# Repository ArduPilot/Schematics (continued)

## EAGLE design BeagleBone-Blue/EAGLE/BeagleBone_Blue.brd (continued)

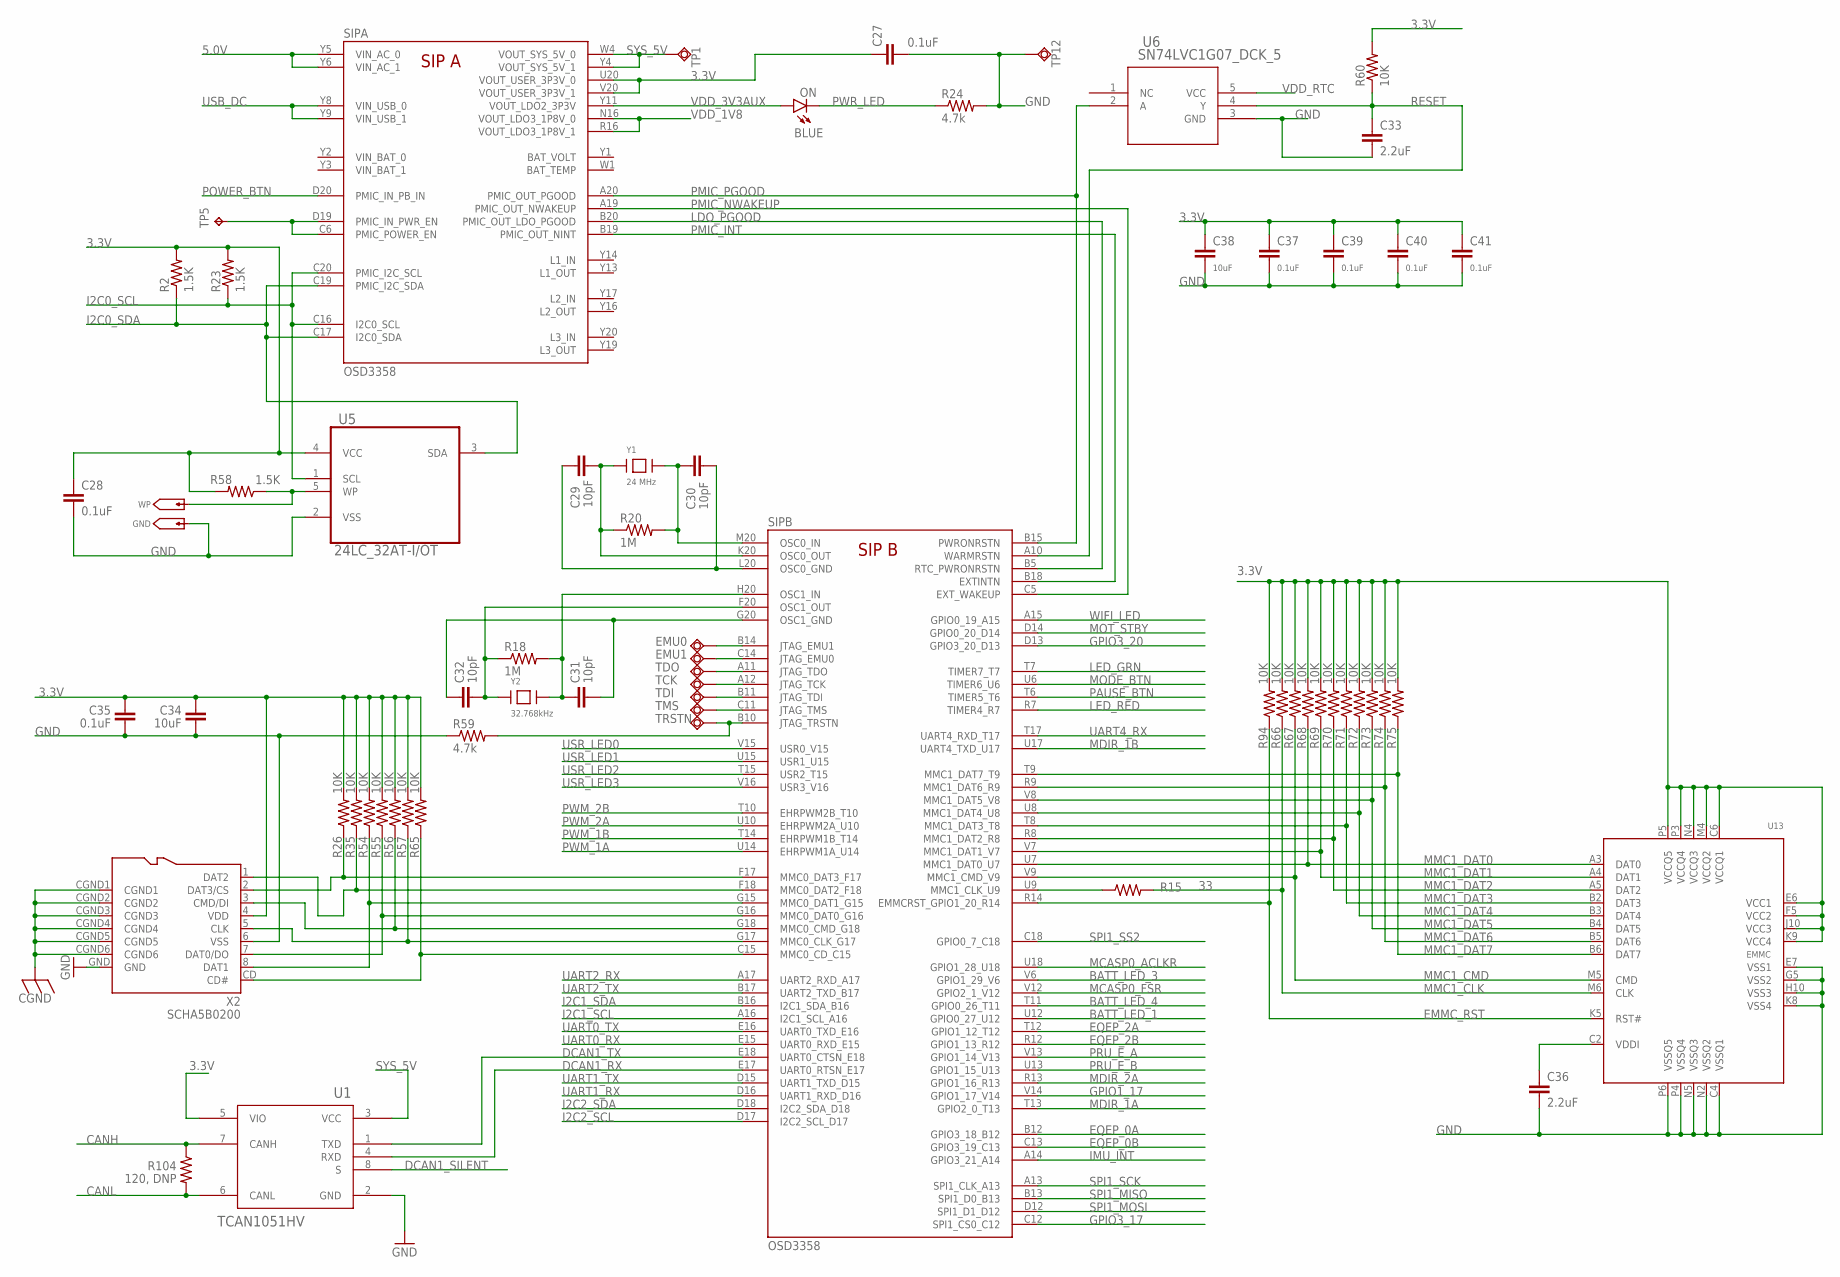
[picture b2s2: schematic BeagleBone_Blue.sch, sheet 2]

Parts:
C27, C28, C35, C37, C39, C40, C41: 0.1uF; 0402-CAP
C29, C30, C31, C32: 10pF; 0402-CAP
C33, C36: 2.2uF; 0402-CAP
C34, C38: 10uF; 0805
EMU0, EMU1: TPSQB1,27; B1,27
GND: GHI2_TESTPAD/W_HOLE_1X1
ON: BLUE; BEAGLEBONE_BLUE_LED-0603
R2, R23, R58: 1.5K; 0402-RES
R15: 33; 0402-RES
R18, R20: 1M; 0402-RES
R24, R59: 4.7k; 0402-RES
R26, R35, R54, R55, R56, R57, R60, R65, R66, R67, R68, R69, R70, R71, R72, R73, R74, R75, R94: 10K; 0402-RES
R104: 120, DNP; 0603-RES
SIP: OSD3358; BEAGLEBONE_BLUE_OSD3358
TCK: TPSQB1,27; B1,27
TDI: TPSQB1,27; B1,27
TDO: TPSQB1,27; B1,27
TMS: TPSQB1,27; B1,27
TP1, TP12: TPSQB1,27; B1,27
TP5: TPB0,65; BEAGLEBONE_BLUE_B0,65
TRSTN: TPSQB1,27; B1,27
U1: TCAN1051HV; BEAGLEBONE_BLUE_D8
U5: 24LC_32AT-I/OT; SOT95P290X145-5N
U6: SN74LVC1G07_DCK_5; BEAGLEBONE_BLUE_DCK5
U13: EMMC; MICRON_EMMC_153
WP: GHI2_TESTPAD/W_HOLE_1X1
X2: SCHA5B0200
Y1: 24 MHz; CRYSTAL_5X3.2MM
Y2: 32.768kHz; CRYSTAL_3.2X1.5

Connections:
3.3V: C27.1, C28.1, C34.2, C35.2, C37.1, C38.1, C39.1, C40.1, C41.1, R2.2, R23.2, R26.2, R35.2, R54.2, R55.2, R56.2, R57.2, R58.2, R60.2, R65.2, R66.2, R67.2, R68.2, R69.2, R70.2, R71.2, R72.2, R73.2, R74.2, R75.2, R94.2, SIP.U20 (VOUT_USER_3P3V_0), SIP.V20 (VOUT_USER_3P3V_1), U1.5 (VIO), U5.4 (VCC), U13.C6 (VCCQ1), U13.E6 (VCC1), U13.F5 (VCC2), U13.J10 (VCC3), U13.K9 (VCC4), U13.M4 (VCCQ2), U13.N4 (VCCQ3), U13.P3 (VCCQ4), U13.P5 (VCCQ5), X2.4 (VDD); also elsewhere on the board
5.0V: SIP.Y5 (VIN_AC_0), SIP.Y6 (VIN_AC_1); also elsewhere on the board
BATT_LED_1: SIP.U12 (GPIO0_27_U12); also elsewhere on the board
BATT_LED_3: SIP.V6 (GPIO1_29_V6); also elsewhere on the board
BATT_LED_4: SIP.T11 (GPIO0_26_T11); also elsewhere on the board
CANH: R104.1, U1.7 (CANH); also elsewhere on the board
CANL: R104.2, U1.6 (CANL); also elsewhere on the board
CGND: X2.CGND1, X2.CGND2, X2.CGND3, X2.CGND4, X2.CGND5, X2.CGND6; also elsewhere on the board
DCAN1_RX: SIP.E17 (UART0_RTSN_E17), U1.4 (RXD)
DCAN1_SILENT: U1.8 (S); also elsewhere on the board
DCAN1_TX: SIP.E18 (UART0_CTSN_E18), U1.1 (TXD)
EMMC_RST: R94.1, SIP.R14 (EMMCRST_GPIO1_20_R14), U13.K5 (RST#)
EQEP_0A: SIP.B12 (GPIO3_18_B12); also elsewhere on the board
EQEP_0B: SIP.C13 (GPIO3_19_C13); also elsewhere on the board
EQEP_2A: SIP.T12 (GPIO1_12_T12); also elsewhere on the board
EQEP_2B: SIP.R12 (GPIO1_13_R12); also elsewhere on the board
GND: C27.2, C28.2, C33.2, C34.1, C35.1, C36.2, C37.2, C38.2, C39.2, C40.2, C41.2, GND.P$1, R24.2, R59.1, TP12.TP, U1.2 (GND), U5.2 (VSS), U6.3 (GND), U13.C4 (VSSQ1), U13.E7 (VSS1), U13.G5 (VSS2), U13.H10 (VSS3), U13.K8 (VSS4), U13.N2 (VSSQ2), U13.N5 (VSSQ3), U13.P4 (VSSQ4), U13.P6 (VSSQ5), X2.6 (VSS), X2.GND; also elsewhere on the board
GPIO1_17: SIP.V14 (GPIO1_17_V14); also elsewhere on the board
GPIO3_17: SIP.C12 (SPI1_CS0_C12); also elsewhere on the board
GPIO3_20: SIP.D13 (GPIO3_20_D13); also elsewhere on the board
I2C0_SCL: R23.1, SIP.C16 (I2C0_SCL), SIP.C20 (PMIC_I2C_SCL), U5.1 (SCL)
I2C0_SDA: R2.1, SIP.C17 (I2C0_SDA), SIP.C19 (PMIC_I2C_SDA), U5.3 (SDA)
I2C1_SCL: SIP.A16 (I2C1_SCL_A16); also elsewhere on the board
I2C1_SDA: SIP.B16 (I2C1_SDA_B16); also elsewhere on the board
I2C2_SCL: SIP.D17 (I2C2_SCL_D17); also elsewhere on the board
I2C2_SDA: SIP.D18 (I2C2_SDA_D18); also elsewhere on the board
IMU_INT: SIP.A14 (GPIO3_21_A14); also elsewhere on the board
LDO_PGOOD: SIP.B5 (RTC_PWRONRSTN), SIP.B20 (PMIC_OUT_LDO_PGOOD)
LED_GRN: SIP.T7 (TIMER7_T7); also elsewhere on the board
LED_RED: SIP.R7 (TIMER4_R7); also elsewhere on the board
MCASP0_ACLKR: SIP.U18 (GPIO1_28_U18); also elsewhere on the board
MCASP0_FSR: SIP.V12 (GPIO2_1_V12); also elsewhere on the board
MDIR_1A: SIP.T13 (GPIO2_0_T13); also elsewhere on the board
MDIR_1B: SIP.U17 (UART4_TXD_U17); also elsewhere on the board
MDIR_2A: SIP.R13 (GPIO1_16_R13); also elsewhere on the board
MMC1_CLK: R15.2, R66.1, U13.M6 (CLK)
MMC1_CMD: R67.1, SIP.V9 (MMC1_CMD_V9), U13.M5 (CMD)
MMC1_DAT0: R68.1, SIP.U7 (MMC1_DAT0_U7), U13.A3 (DAT0)
MMC1_DAT1: R69.1, SIP.V7 (MMC1_DAT1_V7), U13.A4 (DAT1)
MMC1_DAT2: R70.1, SIP.R8 (MMC1_DAT2_R8), U13.A5 (DAT2)
MMC1_DAT3: R71.1, SIP.T8 (MMC1_DAT3_T8), U13.B2 (DAT3)
MMC1_DAT4: R72.1, SIP.U8 (MMC1_DAT4_U8), U13.B3 (DAT4)
MMC1_DAT5: R73.1, SIP.V8 (MMC1_DAT5_V8), U13.B4 (DAT5)
MMC1_DAT6: R74.1, SIP.R9 (MMC1_DAT6_R9), U13.B5 (DAT6)
MMC1_DAT7: R75.1, SIP.T9 (MMC1_DAT7_T9), U13.B6 (DAT7)
MODE_BTN: SIP.U6 (TIMER6_U6); also elsewhere on the board
MOT_STBY: SIP.D14 (GPIO0_20_D14); also elsewhere on the board
unnamed: R57.1, SIP.G17 (MMC0_CLK_G17), X2.5 (CLK)
unnamed: R26.1, SIP.F17 (MMC0_DAT3_F17), X2.2 (DAT3/CS)
unnamed: SIP.C6 (PMIC_POWER_EN), SIP.D19 (PMIC_IN_PWR_EN), TP5.TP
unnamed: C30.1, R20.2, SIP.M20 (OSC0_IN), Y1.2
unnamed: C29.1, R20.1, SIP.K20 (OSC0_OUT), Y1.1
unnamed: R58.1, U5.5 (WP), WP.P$1
unnamed: C29.2, C30.2, SIP.L20 (OSC0_GND)
unnamed: C31.1, R18.2, SIP.H20 (OSC1_IN), Y2.P$2
unnamed: C32.2, R18.1, SIP.F20 (OSC1_OUT), Y2.P$1
unnamed: C31.2, C32.1, SIP.G20 (OSC1_GND)
unnamed: EMU0.TP, SIP.B14 (JTAG_EMU1)
unnamed: EMU1.TP, SIP.C14 (JTAG_EMU0)
unnamed: SIP.A11 (JTAG_TDO), TDO.TP
unnamed: SIP.A12 (JTAG_TCK), TCK.TP
unnamed: SIP.B11 (JTAG_TDI), TDI.TP
unnamed: SIP.C11 (JTAG_TMS), TMS.TP
unnamed: R59.2, SIP.B10 (JTAG_TRSTN), TRSTN.TP
unnamed: R54.1, SIP.G15 (MMC0_DAT1_G15), X2.8 (DAT1)
unnamed: R56.1, SIP.G18 (MMC0_CMD_G18), X2.3 (CMD/DI)
unnamed: R65.1, SIP.C15 (MMC0_CD_C15), X2.CD (CD#)
unnamed: R55.1, SIP.G16 (MMC0_DAT0_G16), X2.7 (DAT0/DO)
unnamed: C36.1, U13.C2 (VDDI)
unnamed: R15.1, SIP.U9 (MMC1_CLK_U9)
NTE: R35.1, SIP.F18 (MMC0_DAT2_F18), X2.1 (DAT2)
PAUSE_BTN: SIP.T6 (TIMER5_T6); also elsewhere on the board
PMIC_INT: SIP.B18 (EXTINTN), SIP.B19 (PMIC_OUT_NINT)
PMIC_NWAKEUP: SIP.A19 (PMIC_OUT_NWAKEUP), SIP.C5 (EXT_WAKEUP)
PMIC_PGOOD: SIP.A20 (PMIC_OUT_PGOOD), SIP.B15 (PWRONRSTN), U6.2 (A)
POWER_BTN: SIP.D20 (PMIC_IN_PB_IN); also elsewhere on the board
PRU_E_A: SIP.V13 (GPIO1_14_V13); also elsewhere on the board
PRU_E_B: SIP.U13 (GPIO1_15_U13); also elsewhere on the board
PWM_1A: SIP.U14 (EHRPWM1A_U14); also elsewhere on the board
PWM_1B: SIP.T14 (EHRPWM1B_T14); also elsewhere on the board
PWM_2A: SIP.U10 (EHRPWM2A_U10); also elsewhere on the board
PWM_2B: SIP.T10 (EHRPWM2B_T10); also elsewhere on the board
PWR_LED: ON.C, R24.1
RESET: C33.1, R60.1, SIP.A10 (WARMRSTN), U6.4 (Y); also elsewhere on the board
SPI1_MISO: SIP.B13 (SPI1_D0_B13); also elsewhere on the board
SPI1_MOSI: SIP.D12 (SPI1_D1_D12); also elsewhere on the board
SPI1_SCK: SIP.A13 (SPI1_CLK_A13); also elsewhere on the board
SPI1_SS2: SIP.C18 (GPIO0_7_C18); also elsewhere on the board
SYS_5V: SIP.W4 (VOUT_SYS_5V_0), SIP.Y4 (VOUT_SYS_5V_1), TP1.TP, U1.3 (VCC); also elsewhere on the board
UART0_RX: SIP.E15 (UART0_RXD_E15); also elsewhere on the board
UART0_TX: SIP.E16 (UART0_TXD_E16); also elsewhere on the board
UART1_RX: SIP.D16 (UART1_RXD_D16); also elsewhere on the board
UART1_TX: SIP.D15 (UART1_TXD_D15); also elsewhere on the board
UART2_RX: SIP.A17 (UART2_RXD_A17); also elsewhere on the board
UART2_TX: SIP.B17 (UART2_TXD_B17); also elsewhere on the board
UART4_RX: SIP.T17 (UART4_RXD_T17); also elsewhere on the board
USB_DC: SIP.Y8 (VIN_USB_0), SIP.Y9 (VIN_USB_1); also elsewhere on the board
USR_LED0: SIP.V15 (USR0_V15); also elsewhere on the board
USR_LED1: SIP.U15 (USR1_U15); also elsewhere on the board
USR_LED2: SIP.T15 (USR2_T15); also elsewhere on the board
USR_LED3: SIP.V16 (USR3_V16); also elsewhere on the board
VDD_1V8: SIP.N16 (VOUT_LDO3_1P8V_0), SIP.R16 (VOUT_LDO3_1P8V_1); also elsewhere on the board
VDD_3V3AUX: ON.A, SIP.Y11 (VOUT_LDO2_3P3V)
VDD_RTC: U6.5 (VCC); also elsewhere on the board
VIN_BAT_0: SIP.Y2 (VIN_BAT_0)
VIN_BAT_1: SIP.Y3 (VIN_BAT_1)
WIFI_LED: SIP.A15 (GPIO0_19_A15); also elsewhere on the board

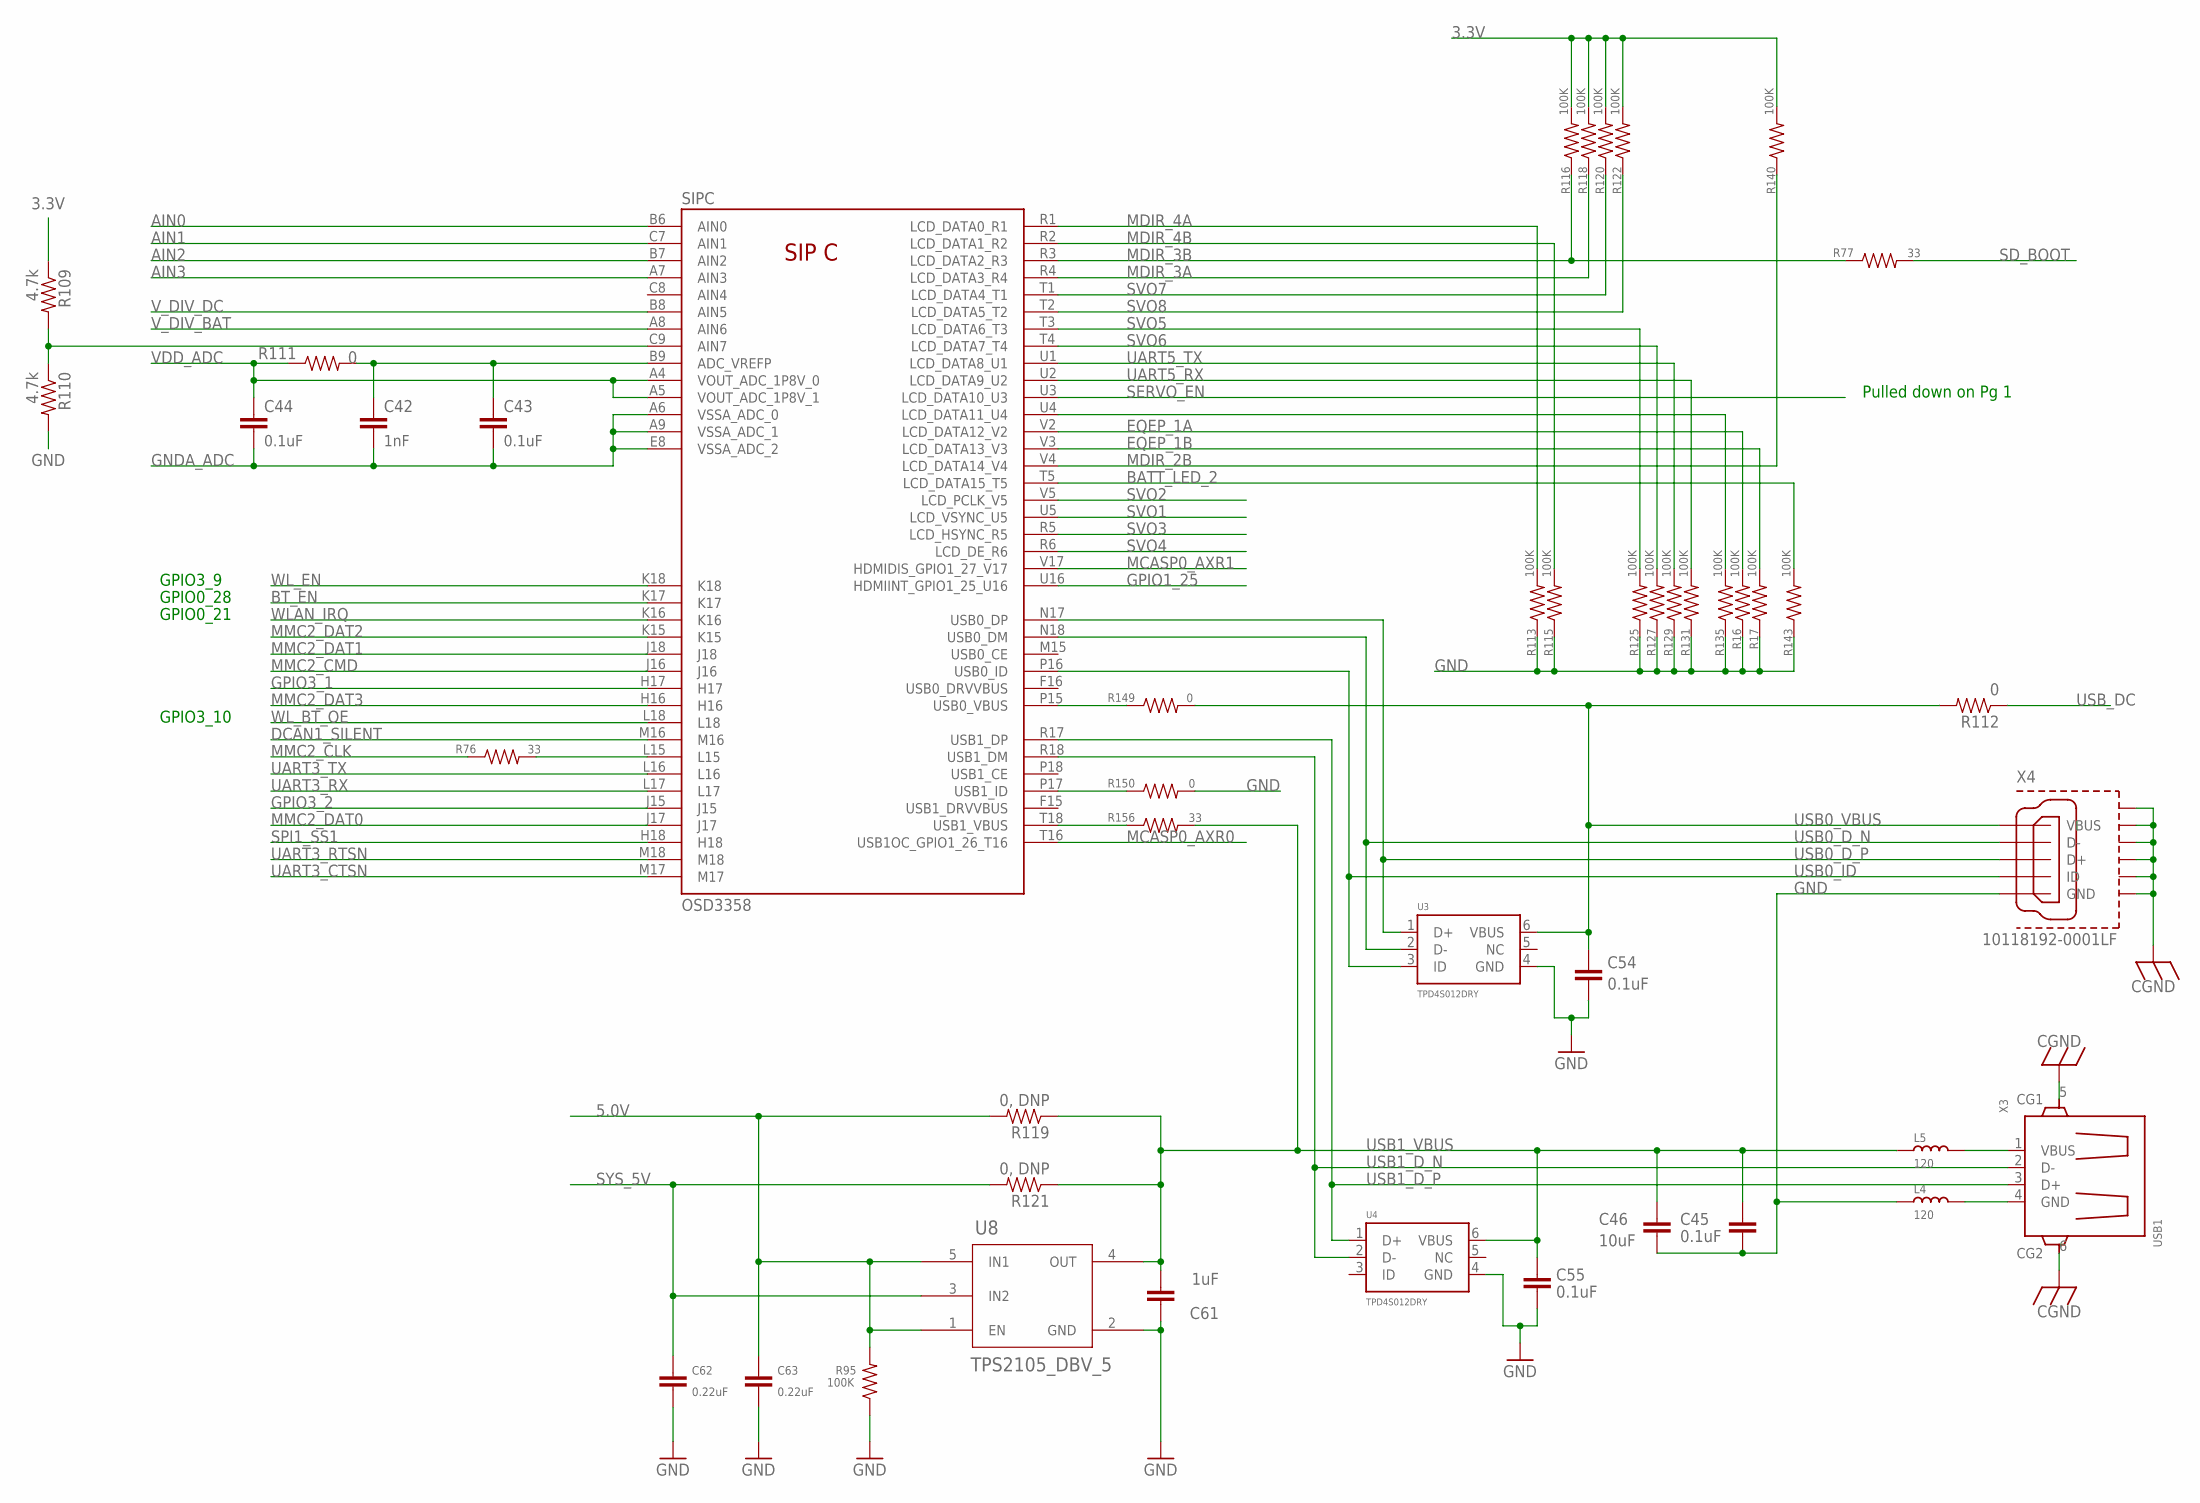
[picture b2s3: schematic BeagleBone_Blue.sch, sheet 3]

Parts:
C42: 1nF; 0402-CAP
C43, C44, C45, C54, C55: 0.1uF; 0402-CAP
C46: 10uF; 0805
C61: 1uF; 0402-CAP
C62, C63: 0.22uF; 0402-CAP
L4, L5: 120; L0603
R16, R17, R95, R113, R115, R116, R118, R120, R122, R125, R127, R129, R131, R135, R140, R143: 100K; 0402-RES
R76, R77, R156: 33; 0402-RES
R109, R110: 4.7k; 0402-RES
R111, R149, R150: 0; 0402-RES
R112: 0; 0603-RES
R119, R121: 0, DNP; 0603-RES
SIP: OSD3358; BEAGLEBONE_BLUE_OSD3358
U3, U4: TPD4S012DRY; SON-6(TI)-DRY
U8: TPS2105_DBV_5; DBV5
X3: USB1; USB_HOST_HORIZONTAL_W/CHASSIS_GND
X4: 10118192-0001LF; 10118192-0001LF(MICRO-USB-B-AMPHENOL-FCI)

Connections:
3.3V: R109.1, R116.2, R118.2, R120.2, R122.2, R140.2; also elsewhere on the board
5.0V: C63.1, R95.2, R119.2, U8.1 (EN), U8.5 (IN1); also elsewhere on the board
AIN0: SIP.B6 (AIN0); also elsewhere on the board
AIN1: SIP.C7 (AIN1); also elsewhere on the board
AIN2: SIP.B7 (AIN2); also elsewhere on the board
AIN3: SIP.A7 (AIN3); also elsewhere on the board
BATT_LED_2: R143.2, SIP.T5 (LCD_DATA15_T5); also elsewhere on the board
BT_EN: SIP.K17; also elsewhere on the board
CGND: X3.5 (CG1), X3.6 (CG2), X4.CGND1 (SGND1), X4.CGND2 (SGND2), X4.CGND3 (SGND3), X4.CGND4 (SGND4), X4.CGND5 (SGND5), X4.CGND6 (SGND6); also elsewhere on the board
DCAN1_SILENT: SIP.M16; also elsewhere on the board
EQEP_1A: R16.2, SIP.V2 (LCD_DATA12_V2); also elsewhere on the board
EQEP_1B: R17.2, SIP.V3 (LCD_DATA13_V3); also elsewhere on the board
GND: C45.2, C46.2, C54.2, C55.2, C61.1, C62.2, C63.2, L4.1, R16.1, R17.1, R95.1, R110.2, R113.1, R115.1, R125.1, R127.1, R129.1, R131.1, R135.1, R143.1, R150.2, U3.4 (GND), U4.4 (GND), U8.2 (GND), X4.GND; also elsewhere on the board
GNDA_ADC: C42.2, C43.2, C44.2, SIP.A6 (VSSA_ADC_0), SIP.A9 (VSSA_ADC_1), SIP.E8 (VSSA_ADC_2)
GPIO1_25: SIP.U16 (HDMIINT_GPIO1_25_U16); also elsewhere on the board
GPIO3_1: SIP.H17; also elsewhere on the board
GPIO3_2: SIP.J15; also elsewhere on the board
MCASP0_AXR0: SIP.T16 (USB1OC_GPIO1_26_T16); also elsewhere on the board
MCASP0_AXR1: SIP.V17 (HDMIDIS_GPIO1_27_V17); also elsewhere on the board
MDIR_2B: R140.1, SIP.V4 (LCD_DATA14_V4); also elsewhere on the board
MDIR_3A: R118.1, SIP.R4 (LCD_DATA3_R4); also elsewhere on the board
MDIR_3B: R77.1, R116.1, SIP.R3 (LCD_DATA2_R3); also elsewhere on the board
MDIR_4A: R113.2, SIP.R1 (LCD_DATA0_R1); also elsewhere on the board
MDIR_4B: R115.2, SIP.R2 (LCD_DATA1_R2); also elsewhere on the board
MMC2_CLK: R76.1; also elsewhere on the board
MMC2_CMD: SIP.J16; also elsewhere on the board
MMC2_DAT0: SIP.J17; also elsewhere on the board
MMC2_DAT1: SIP.J18; also elsewhere on the board
MMC2_DAT2: SIP.K15; also elsewhere on the board
MMC2_DAT3: SIP.H16; also elsewhere on the board
unnamed: R76.2, SIP.L15
unnamed: R135.2, SIP.U4 (LCD_DATA11_U4)
unnamed: C42.1, C43.1, R111.2, SIP.B9 (ADC_VREFP)
unnamed: R109.2, R110.1, SIP.C9 (AIN7)
unnamed: R149.1, SIP.P15 (USB0_VBUS)
unnamed: R150.1, SIP.P17 (USB1_ID)
unnamed: L4.2, X3.4 (GND)
unnamed: R156.1, SIP.T18 (USB1_VBUS)
unnamed: L5.2, X3.1 (VBUS)
SD_BOOT: R77.2; also elsewhere on the board
SERVO_EN: SIP.U3 (LCD_DATA10_U3); also elsewhere on the board
SPI1_SS1: SIP.H18; also elsewhere on the board
SVO1: SIP.U5 (LCD_VSYNC_U5); also elsewhere on the board
SVO2: SIP.V5 (LCD_PCLK_V5); also elsewhere on the board
SVO3: SIP.R5 (LCD_HSYNC_R5); also elsewhere on the board
SVO4: SIP.R6 (LCD_DE_R6); also elsewhere on the board
SVO5: R125.2, SIP.T3 (LCD_DATA6_T3); also elsewhere on the board
SVO6: R127.2, SIP.T4 (LCD_DATA7_T4); also elsewhere on the board
SVO7: R120.1, SIP.T1 (LCD_DATA4_T1); also elsewhere on the board
SVO8: R122.1, SIP.T2 (LCD_DATA5_T2); also elsewhere on the board
SYS_5V: C62.1, R121.2, U8.3 (IN2); also elsewhere on the board
UART3_CTSN: SIP.M17; also elsewhere on the board
UART3_RTSN: SIP.M18; also elsewhere on the board
UART3_RX: SIP.L17; also elsewhere on the board
UART3_TX: SIP.L16; also elsewhere on the board
UART5_RX: R131.2, SIP.U2 (LCD_DATA9_U2); also elsewhere on the board
UART5_TX: R129.2, SIP.U1 (LCD_DATA8_U1); also elsewhere on the board
USB0_D_N: SIP.N18 (USB0_DM), U3.2 (D-), X4.D-
USB0_D_P: SIP.N17 (USB0_DP), U3.1 (D+), X4.D+
USB0_ID: SIP.P16 (USB0_ID), U3.3 (ID), X4.ID
USB0_VBUS: C54.1, R112.2, R149.2, U3.6 (VBUS), X4.VBUS
USB1_D_N: SIP.R18 (USB1_DM), U4.2 (D-), X3.2 (D-)
USB1_D_P: SIP.R17 (USB1_DP), U4.1 (D+), X3.3 (D+)
USB1_VBUS: C45.1, C46.1, C55.1, C61.2, L5.1, R119.1, R121.1, R156.2, U4.6 (VBUS), U8.4 (OUT)
USB_DC: R112.1; also elsewhere on the board
VDD_ADC: C44.1, R111.1, SIP.A4 (VOUT_ADC_1P8V_0), SIP.A5 (VOUT_ADC_1P8V_1); also elsewhere on the board
VIN_BAT_0: SIP.Y2 (VIN_BAT_0)
VIN_BAT_1: SIP.Y3 (VIN_BAT_1)
V_DIV_BAT: SIP.A8 (AIN6); also elsewhere on the board
V_DIV_DC: SIP.B8 (AIN5); also elsewhere on the board
WLAN_IRQ: SIP.K16; also elsewhere on the board
WL_BT_OE: SIP.L18; also elsewhere on the board
WL_EN: SIP.K18; also elsewhere on the board

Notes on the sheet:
Pulled down on Pg 1
GPIO3_9
GPIO0_28
GPIO0_21
GPIO3_10

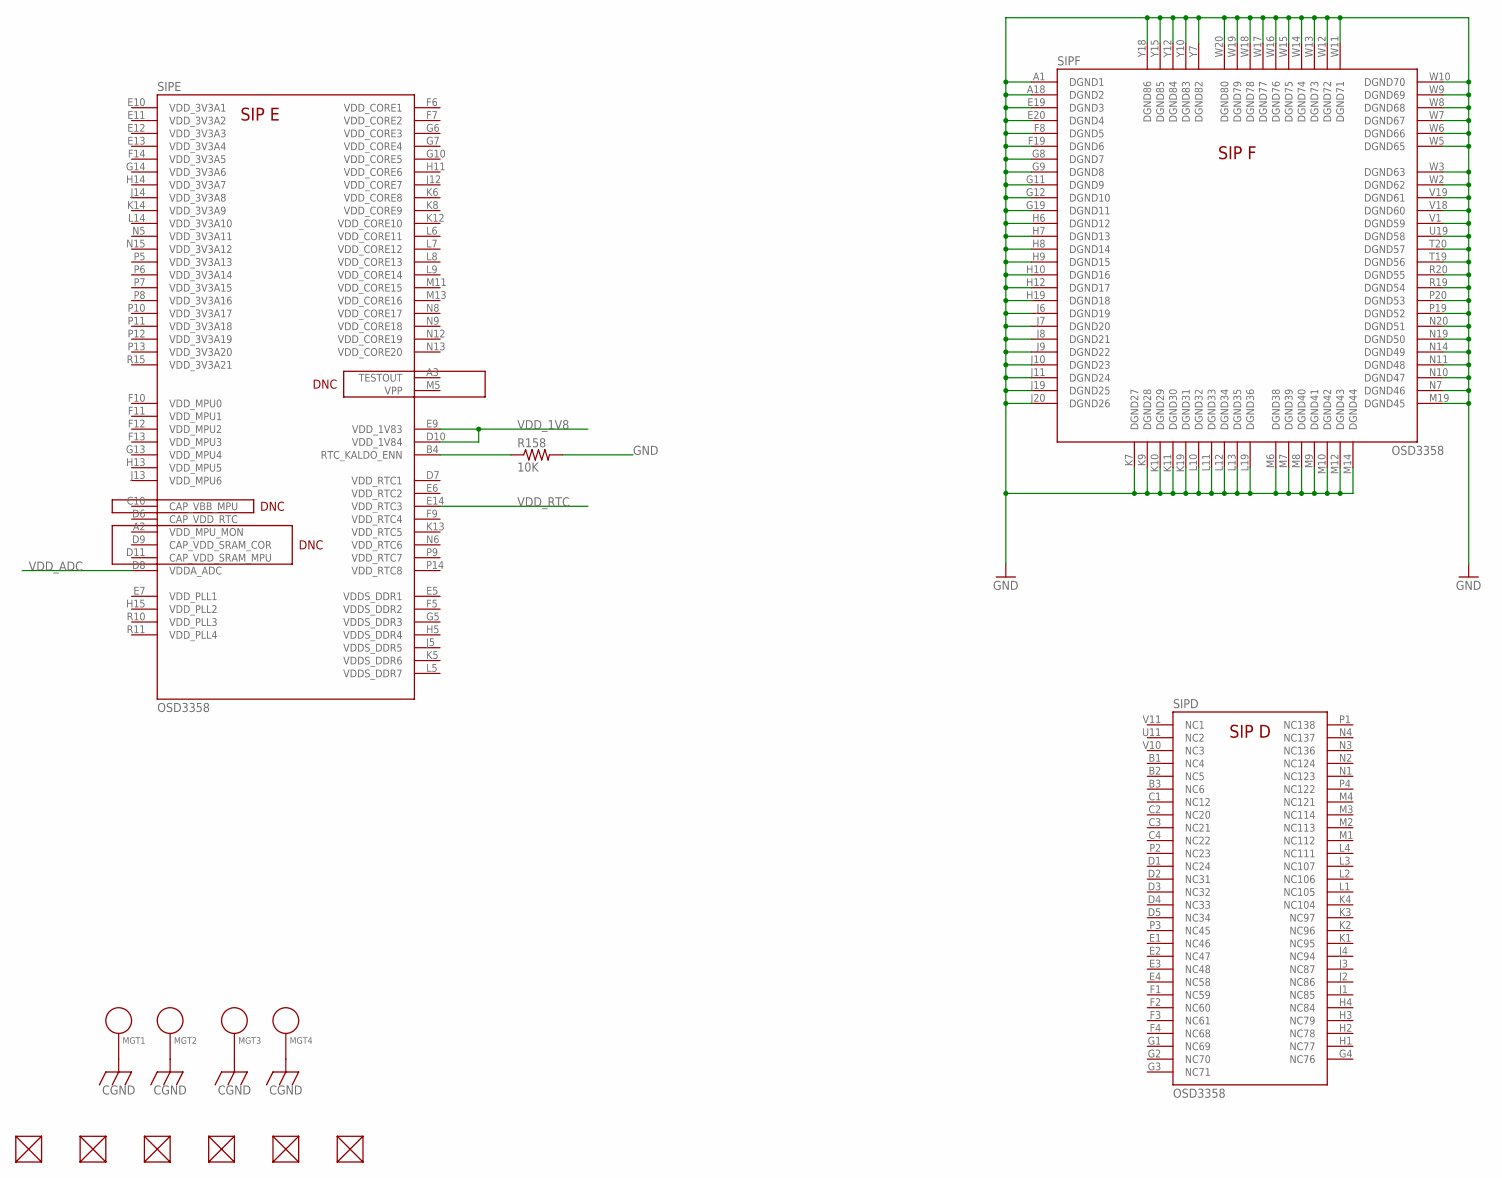
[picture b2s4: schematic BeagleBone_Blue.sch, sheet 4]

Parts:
FUD1, FUD2, FUD3, FUD4, FUD5, FUD6: FIDUCIAL; FIDUCIAL_40MIL
MGT1, MGT2, MGT3, MGT4: MOUNTING_HOLE
R158: 10K; 0402-RES
SIP: OSD3358; BEAGLEBONE_BLUE_OSD3358

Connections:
CGND: MGT1.P$1, MGT2.P$1, MGT3.P$1, MGT4.P$1; also elsewhere on the board
GND: R158.2, SIP.A1 (DGND1), SIP.A18 (DGND2), SIP.E19 (DGND3), SIP.E20 (DGND4), SIP.F8 (DGND5), SIP.F19 (DGND6), SIP.G8 (DGND7), SIP.G9 (DGND8), SIP.G11 (DGND9), SIP.G12 (DGND10), SIP.G19 (DGND11), SIP.H6 (DGND12), SIP.H7 (DGND13), SIP.H8 (DGND14), SIP.H9 (DGND15), SIP.H10 (DGND16), SIP.H12 (DGND17), SIP.H19 (DGND18), SIP.J6 (DGND19), SIP.J7 (DGND20), SIP.J8 (DGND21), SIP.J9 (DGND22), SIP.J10 (DGND23), SIP.J11 (DGND24), SIP.J19 (DGND25), SIP.J20 (DGND26), SIP.K7 (DGND27), SIP.K9 (DGND28), SIP.K10 (DGND29), SIP.K11 (DGND30), SIP.K19 (DGND31), SIP.L10 (DGND32), SIP.L11 (DGND33), SIP.L12 (DGND34), SIP.L13 (DGND35), SIP.L19 (DGND36), SIP.M6 (DGND38), SIP.M7 (DGND39), SIP.M8 (DGND40), SIP.M9 (DGND41), SIP.M10 (DGND42), SIP.M12 (DGND43), SIP.M14 (DGND44), SIP.M19 (DGND45), SIP.N7 (DGND46), SIP.N10 (DGND47), SIP.N11 (DGND48), SIP.N14 (DGND49), SIP.N19 (DGND50), SIP.N20 (DGND51), SIP.P19 (DGND52), SIP.P20 (DGND53), SIP.R19 (DGND54), SIP.R20 (DGND55), SIP.T19 (DGND56), SIP.T20 (DGND57), SIP.U19 (DGND58), SIP.V1 (DGND59), SIP.V18 (DGND60), SIP.V19 (DGND61), SIP.W2 (DGND62), SIP.W3 (DGND63), SIP.W5 (DGND65), SIP.W6 (DGND66), SIP.W7 (DGND67), SIP.W8 (DGND68), SIP.W9 (DGND69), SIP.W10 (DGND70), SIP.W11 (DGND71), SIP.W12 (DGND72), SIP.W13 (DGND73), SIP.W14 (DGND74), SIP.W15 (DGND75), SIP.W16 (DGND76), SIP.W17 (DGND77), SIP.W18 (DGND78), SIP.W19 (DGND79), SIP.W20 (DGND80), SIP.Y7 (DGND82), SIP.Y10 (DGND83), SIP.Y12 (DGND84), SIP.Y15 (DGND85), SIP.Y18 (DGND86); also elsewhere on the board
unnamed: R158.1, SIP.B4 (RTC_KALDO_ENN)
VDD_1V8: SIP.D10 (VDD_1V84), SIP.E9 (VDD_1V83); also elsewhere on the board
VDD_ADC: SIP.D8 (VDDA_ADC); also elsewhere on the board
VDD_RTC: SIP.E14 (VDD_RTC3); also elsewhere on the board
VIN_BAT_0: SIP.Y2 (VIN_BAT_0)
VIN_BAT_1: SIP.Y3 (VIN_BAT_1)

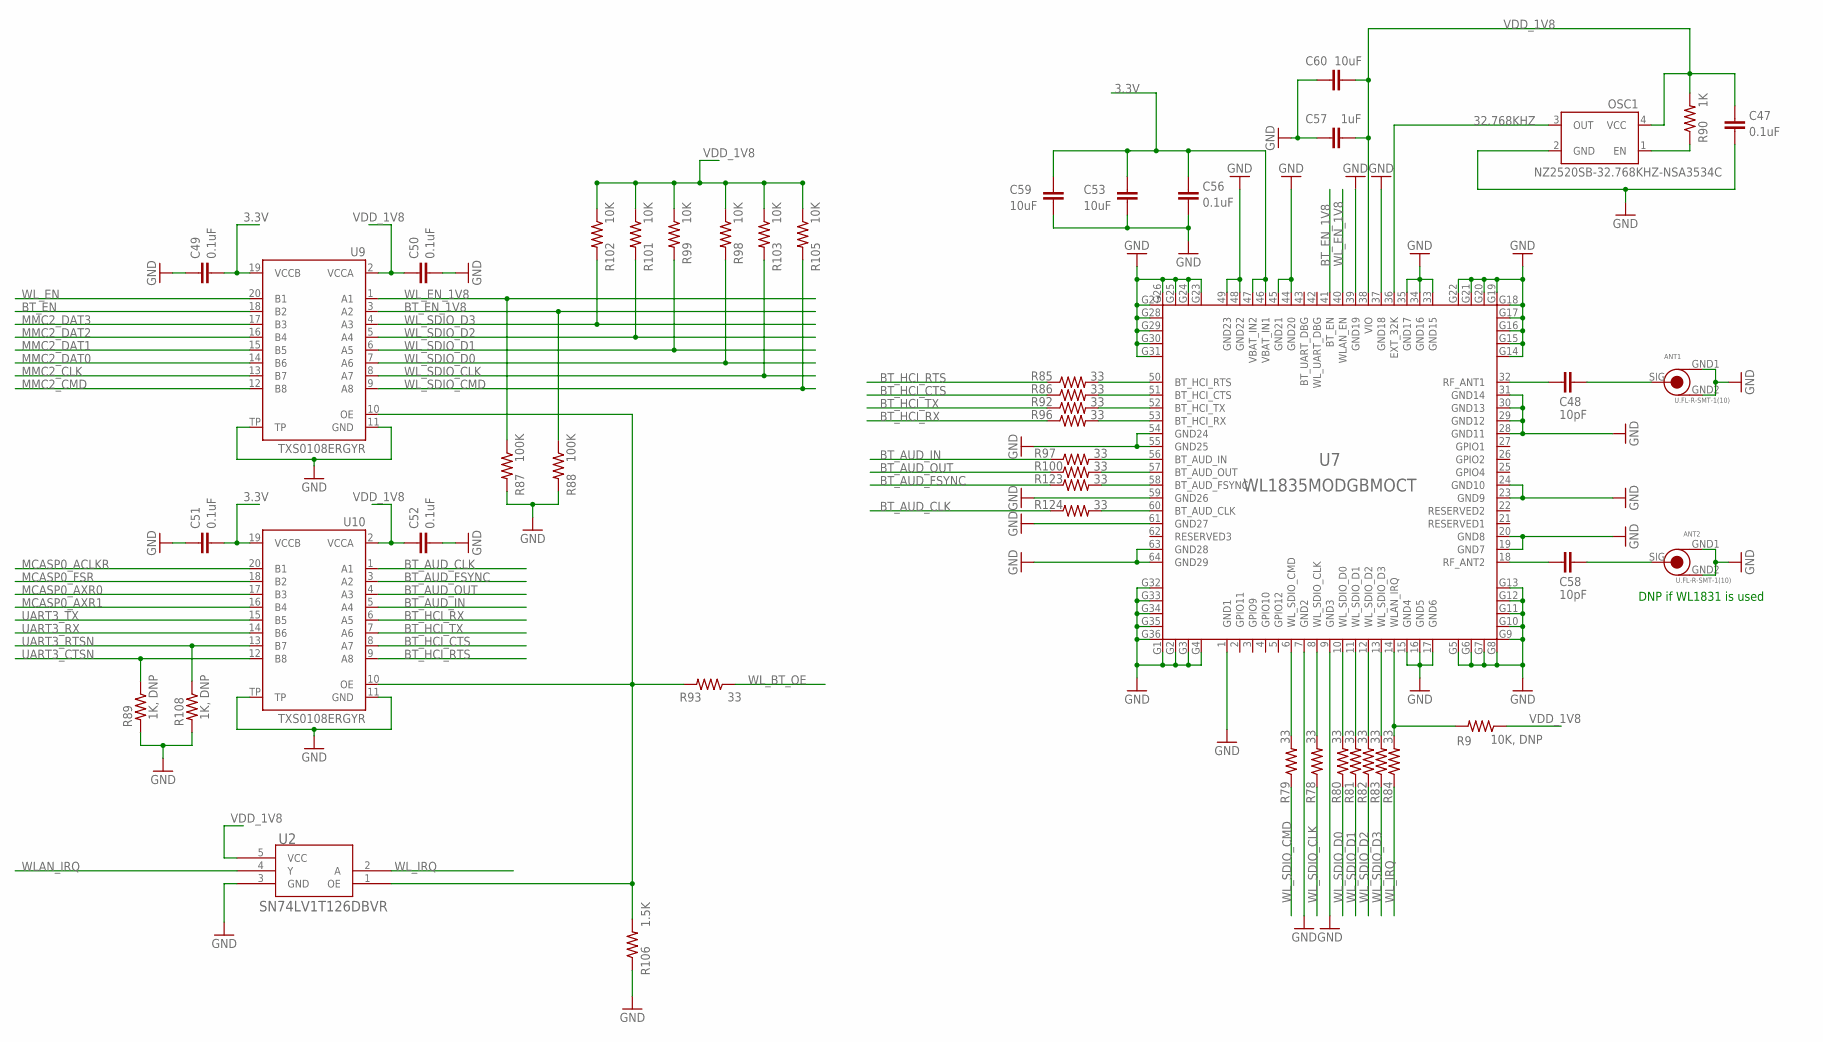
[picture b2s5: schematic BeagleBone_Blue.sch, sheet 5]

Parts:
ANT1, ANT2: U.FL-R-SMT-1(10); U.FL-R-SMT-1
C47, C49, C50, C51, C52, C56: 0.1uF; 0402-CAP
C48, C58: 10pF; 0402-CAP
C53, C59, C60: 10uF; 0805
C57: 1uF; 0402-CAP
OSC1: NZ2520SB-32.768KHZ-NSA3534C; NZ2520S
R9: 10K, DNP; 0402-RES
R78, R79, R80, R81, R82, R83, R84, R85, R86, R92, R93, R96, R97, R100, R123, R124: 33; 0402-RES
R87, R88: 100K; 0402-RES
R89, R108: 1K, DNP; 0402-RES
R90: 1K; 0402-RES
R98, R99, R101, R102, R103, R105: 10K; 0402-RES
R106: 1.5K; 0402-RES
U2: SN74LV1T126DBVR; BEAGLEBONE_BLUE_SOT23-5
U7: WL1835MODGBMOCT; MOC-100(TI)
U9, U10: TXS0108ERGYR; R-PVQFN-N20(TI)

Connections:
3.3V: C49.2, C51.2, C53.1, C56.1, C59.1, U7.46 (VBAT_IN1), U7.47 (VBAT_IN2), U9.19 (VCCB), U10.19 (VCCB); also elsewhere on the board
32.768KHZ: OSC1.3 (OUT), U7.36 (EXT_32K)
ALT.BUFF.OE: R93.2, R106.2, U2.1 (OE), U9.10 (OE), U10.10 (OE)
ANT1_A: C48.2, U7.32 (RF_ANT1)
ANT1_B: ANT1.SIG, C48.1
ANT2_A: C58.2, U7.18 (RF_ANT2)
ANT2_B: ANT2.SIG, C58.1
BT_AUD_CLK: R124.1, U10.1 (A1)
BT_AUD_FSYNC: R123.1, U10.3 (A2)
BT_AUD_IN: R97.1, U10.5 (A4)
BT_AUD_OUT: R100.1, U10.4 (A3)
BT_EN: U9.18 (B2); also elsewhere on the board
BT_EN_1V8: R88.1, U7.41 (BT_EN), U9.3 (A2)
BT_HCI_CTS: R86.1, U10.8 (A7)
BT_HCI_RTS: R85.1, U10.9 (A8)
BT_HCI_RX: R96.1, U10.6 (A5)
BT_HCI_TX: R92.1, U10.7 (A6)
GND: ANT1.GND1, ANT1.GND2, ANT2.GND1, ANT2.GND2, C47.2, C49.1, C50.2, C51.1, C52.2, C53.2, C56.2, C57.1, C59.2, C60.1, OSC1.2 (GND), R87.2, R88.2, R89.2, R106.1, R108.2, U2.3 (GND), U7.1 (GND1), U7.7 (GND2), U7.9 (GND3), U7.15 (GND4), U7.16 (GND5), U7.17 (GND6), U7.19 (GND7), U7.20 (GND8), U7.23 (GND9), U7.24 (GND10), U7.28 (GND11), U7.29 (GND12), U7.30 (GND13), U7.31 (GND14), U7.33 (GND15), U7.34 (GND16), U7.35 (GND17), U7.37 (GND18), U7.39 (GND19), U7.44 (GND20), U7.45 (GND21), U7.48 (GND22), U7.49 (GND23), U7.54 (GND24), U7.55 (GND25), U7.59 (GND26), U7.61 (GND27), U7.63 (GND28), U7.64 (GND29), U7.G1, U7.G2, U7.G3, U7.G4, U7.G5, U7.G6, U7.G7, U7.G8, U7.G9, U7.G10, U7.G11, U7.G12, U7.G13, U7.G14, U7.G15, U7.G16, U7.G17, U7.G18, U7.G19, U7.G20, U7.G21, U7.G22, U7.G23, U7.G24, U7.G25, U7.G26, U7.G27, U7.G28, U7.G29, U7.G30, U7.G31, U7.G32, U7.G33, U7.G34, U7.G35, U7.G36, U9.11 (GND), U9.TP, U10.11 (GND), U10.TP; also elsewhere on the board
MCASP0_ACLKR: U10.20 (B1); also elsewhere on the board
MCASP0_AXR0: U10.17 (B3); also elsewhere on the board
MCASP0_AXR1: U10.16 (B4); also elsewhere on the board
MCASP0_FSR: U10.18 (B2); also elsewhere on the board
MMC2_CLK: U9.13 (B7); also elsewhere on the board
MMC2_CMD: U9.12 (B8); also elsewhere on the board
MMC2_DAT0: U9.14 (B6); also elsewhere on the board
MMC2_DAT1: U9.15 (B5); also elsewhere on the board
MMC2_DAT2: U9.16 (B4); also elsewhere on the board
MMC2_DAT3: U9.17 (B3); also elsewhere on the board
unnamed: OSC1.1 (EN), R90.1
unnamed: R100.2, U7.57 (BT_AUD_OUT)
unnamed: R9.2, R84.2, U7.14 (WLAN_IRQ)
unnamed: R83.2, U7.13 (WL_SDIO_D3)
unnamed: R82.2, U7.12 (WL_SDIO_D2)
unnamed: R81.2, U7.11 (WL_SDIO_D1)
unnamed: R80.2, U7.10 (WL_SDIO_D0)
unnamed: R78.2, U7.8 (WL_SDIO_CLK)
unnamed: R79.2, U7.6 (WL_SDIO_CMD)
unnamed: R85.2, U7.50 (BT_HCI_RTS)
unnamed: R86.2, U7.51 (BT_HCI_CTS)
unnamed: R92.2, U7.52 (BT_HCI_TX)
unnamed: R96.2, U7.53 (BT_HCI_RX)
unnamed: R97.2, U7.56 (BT_AUD_IN)
unnamed: R123.2, U7.58 (BT_AUD_FSYNC)
unnamed: R124.2, U7.60 (BT_AUD_CLK)
UART3_CTSN: R89.1, U10.12 (B8); also elsewhere on the board
UART3_RTSN: R108.1, U10.13 (B7); also elsewhere on the board
UART3_RX: U10.14 (B6); also elsewhere on the board
UART3_TX: U10.15 (B5); also elsewhere on the board
VDD_1V8: C47.1, C50.1, C52.1, C57.2, C60.2, OSC1.4 (VCC), R9.1, R90.2, R98.1, R99.1, R101.1, R102.1, R103.1, R105.1, U2.5 (VCC), U7.38 (VIO), U9.2 (VCCA), U10.2 (VCCA); also elsewhere on the board
WLAN_IRQ: U2.4 (Y); also elsewhere on the board
WL_BT_OE: R93.1; also elsewhere on the board
WL_EN: U9.20 (B1); also elsewhere on the board
WL_EN_1V8: R87.1, U7.40 (WLAN_EN), U9.1 (A1)
WL_IRQ: R84.1, U2.2 (A)
WL_SDIO_CLK: R78.1, R103.2, U9.8 (A7)
WL_SDIO_CMD: R79.1, R105.2, U9.9 (A8)
WL_SDIO_D0: R80.1, R98.2, U9.7 (A6)
WL_SDIO_D1: R81.1, R99.2, U9.6 (A5)
WL_SDIO_D2: R82.1, R101.2, U9.5 (A4)
WL_SDIO_D3: R83.1, R102.2, U9.4 (A3)

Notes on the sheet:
DNP if WL1831 is used
